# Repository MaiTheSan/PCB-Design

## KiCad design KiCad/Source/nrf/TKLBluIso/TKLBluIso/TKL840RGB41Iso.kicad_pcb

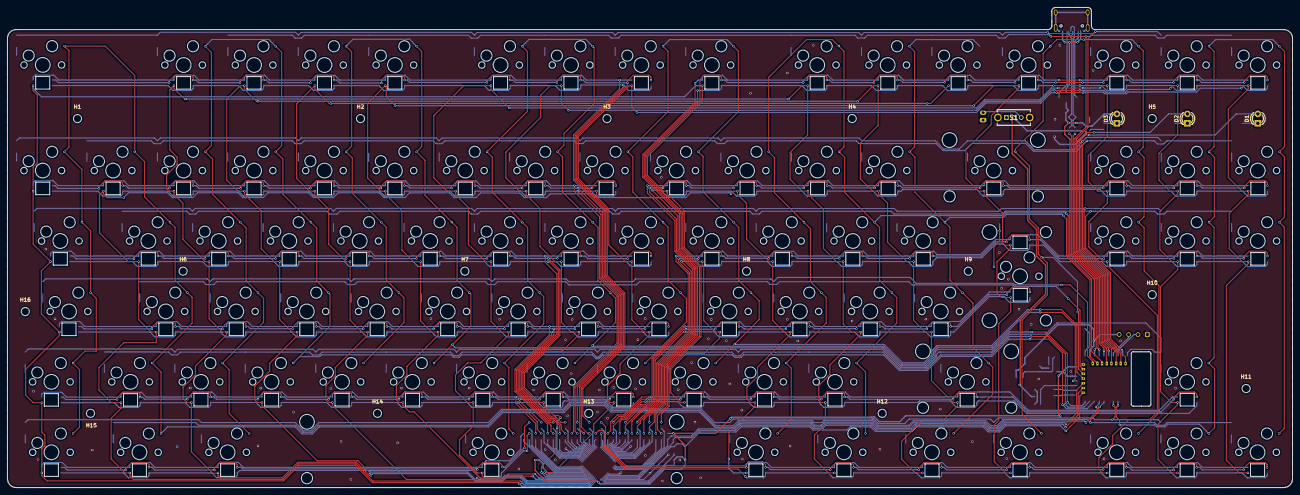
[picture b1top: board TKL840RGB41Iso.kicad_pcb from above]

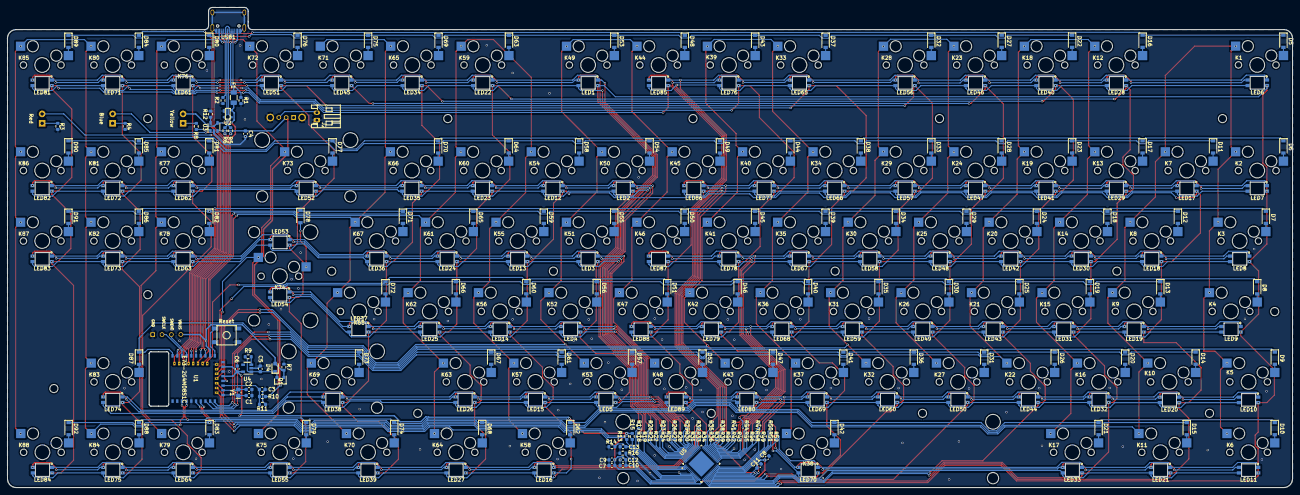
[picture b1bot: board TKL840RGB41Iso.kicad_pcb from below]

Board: 2 copper layers, 347.6 x 129.8 mm, 363 parts (255 on the bottom side), 221 nets.

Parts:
C1, C2: 22pF; C_0603_1608Metric
C3: 1nF; C_0603_1608Metric
C4, C5, C6: 10uF; C_0603_1608Metric
C7, C8, C9: 1uF; C_0603_1608Metric
C10, C11, C12, C13: 0.1uF; C_0603_1608Metric
D1: Red; LED_D3.0mm
D2: Blue; LED_D3.0mm
D3: Yellow; LED_D3.0mm
D4: 1N5819; D_SOD-323F
D5, D6, D7, D8, D9, D10, D11, D12, D13, D14, D15, D16, D17, D18, D19, D20, D21, D22, D23, D24, D25, D26, D27, D28, D29, D30, D31, D32, D33, D34, D35, D36, D37, D38, D39, D40, D41, D42, D43, D44, D45, D46, D47, D48, D49, D50, D51, D52, D53, D54, D55, D56, D57, D58, D59, D60, D61, D62, D63, D64, D65, D66, D67, D68, D69, D70, D71, D72, D73, D74, D75, D76, D77, D78, D79, D80, D81, D82, D83, D84, D85, D86, D87, D88, D89, D90, D91, D92: D; D_SOD-123
F1: 500mA; Fuse_1206_3216Metric
H1, H2, H3, H4, H5, H6, H7, H8, H9, H10, H11, H12, H13, H14, H15, H16: MountingHole; MountingHole_2.2mm_M2
J1: Conn_01x04; connector_usb
J2: Conn_01x02; JST_PH_S2B-PH-K_1x02_P2.00mm_Horizontal
K1, K2, K7, K8, K9, K10, K12, K13, K14, K15, K16, K18, K19, K20, K21, K22, K23, K24, K25, K26, K27, K28, K29, K30, K31, K32, K33, K34, K35, K36, K37, K39, K40, K41, K42, K43, K44, K45, K46, K47, K48, K49, K50, K51, K52, K53, K54, K55, K56, K57, K59, K60, K61, K62, K63, K65, K66, K67, K68, K71, K72, K76, K77, K78, K79, K80, K81, K82, K83, K84, K85, K86, K87, K88: KEYSW; MXOnly-1U-Hotswap
K3: KEYSW; MXOnly-1.5U-Hotswap
K4: KEYSW; MXOnly-1.75U-Hotswap
K5, K6, K11, K17, K58, K64, K70, K75: KEYSW; MXOnly-1.25U-Hotswap
K38: KEYSW; MXOnly-6.25U-Hotswap-ReversedStabilizers
K69: KEYSW; MXOnly-2.75U-Hotswap-ReversedStabilizers
K73, K74: KEYSW; MXOnly-2U-Hotswap-ReversedStabilizers
LED1, LED2, LED3, LED4, LED5, LED6, LED7, LED8, LED9, LED10, LED11, LED12, LED13, LED14, LED15, LED16, LED17, LED18, LED19, LED20, LED21, LED22, LED23, LED24, LED25, LED26, LED27, LED28, LED29, LED30, LED31, LED32, LED33, LED34, LED35, LED36, LED37, LED38, LED39, LED40, LED41, LED42, LED43, LED44, LED45, LED46, LED47, LED48, LED49, LED50, LED51, LED52, LED53, LED54, LED55, LED56, LED57, LED58, LED59, LED60, LED61, LED62, LED63, LED64, LED65, LED66, LED67, LED68, LED69, LED70, LED71, LED72, LED73, LED74, LED75, LED76, LED77, LED78, LED79, LED80, LED81, LED82, LED83, LED84, LED85, LED86, LED87, LED88, LED89: RGB-6028
Q1: AO3407; SOT-23
R1, R2: 5.1k; R_0603_1608Metric
R3, R4, R8, R13, R15: 1k; R_0603_1608Metric
R5, R6: 22; R_0603_1608Metric
R7, R9, R14, R16: 100k; R_0603_1608Metric
R10: 806k; R_0603_1608Metric
R11: 2M; R_0603_1608Metric
R12: 1.25k; R_0603_1608Metric
R17, R20, R23, R26, R29, R32, R35, R38, R41, R44, R47, R50: 51k; R_0603_1608Metric
R18, R19, R21, R22, R24, R25, R27, R28, R30, R31, R33, R34, R36, R37, R39, R40, R42, R43, R45, R46, R48, R49, R51, R52: 20k; R_0603_1608Metric
ResetPush1: Reset; SKQG-1155865
S1: EG1249
U1: E73-2G4M08S1C; E73-2G4M08S1C-52840
U2: PRTR5V0U2X; SOT143B
U3: MCP73831-3-OT; SOT-23-5
U4: AP2112K-3.3; SOT-23-5
U5: IS31FL3741; QFN40P700X700X80-61N
USB1: HRO-TYPE-C-31-M-12
Y1: 32.768kHz; Crystal_SMD_MicroCrystal_CM9V-T1A-2Pin_1.6x1.0mm_HandSolder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

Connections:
3.3v: C6.1, C7.1, C8.1, C9.1, C10.1, C11.1, C12.1, R13.1, R15.1, U1.19, U1.23, U4.5, U5.14, U5.15, U5.25
BLUE_LED: D2.2, U1.35
CS1: R52.1, U5.26
CS2: R51.1, U5.27
CS3: R50.1, U5.28
CS4: R49.1, U5.29
CS5: R48.1, U5.30
CS6: R47.1, U5.31
CS7: R46.1, U5.32
CS8: R45.1, U5.33
CS9: R44.1, U5.34
CS10: R43.1, U5.35
CS11: R42.1, U5.37
CS12: R41.1, U5.38
CS13: R40.1, U5.39
CS14: R39.1, U5.40
CS15: R38.1, U5.41
CS16: R37.1, U5.42
CS17: R36.1, U5.43
CS18: R35.1, U5.44
CS19: R34.1, U5.45
CS20: R33.1, U5.46
CS21: R32.1, U5.47
CS22: R31.1, U5.48
CS23: R30.1, U5.49
CS24: R29.1, U5.50
CS25: R28.1, U5.51
CS26: R27.1, U5.52
CS27: R26.1, U5.53
CS28: R25.1, U5.54
CS29: R24.1, U5.56
CS30: R23.1, U5.57
CS31: R22.1, U5.58
CS32: R21.1, U5.59
CS33: R20.1, U5.60
CS34: R19.1, U5.1
CS35: R18.1, U5.2
CS36: R17.1, U5.3
Col1: K1.1, K2.1, K3.1, K4.1, K5.1, K6.1, K7.1, K8.1, K9.1, K10.1, K11.1, U1.7
Col2: K12.1, K13.1, K14.1, K15.1, K16.1, K17.1, K18.1, K19.1, K20.1, K21.1, K22.1, U1.8
Col3: K23.1, K24.1, K25.1, K26.1, K27.1, K28.1, K29.1, K30.1, K31.1, K32.1, U1.10
Col4: K33.1, K34.1, K35.1, K36.1, K37.1, K38.1, K39.1, K40.1, K41.1, K42.1, K43.1, U1.17
Col5: K44.1, K45.1, K46.1, K47.1, K48.1, K49.1, K50.1, K51.1, K52.1, K53.1, U1.18
Col6: K54.1, K55.1, K56.1, K57.1, K58.1, K59.1, K60.1, K61.1, K62.1, K63.1, K64.1, U1.32
Col7: K65.1, K66.1, K67.1, K68.1, K69.1, K70.1, K71.1, U1.30
Col8: K72.1, K73.1, K74.1, K75.1, K76.1, K77.1, K78.1, K79.1, U1.20
Col9: K80.1, K81.1, K82.1, K83.1, K84.1, K85.1, K86.1, K87.1, K88.1, U1.3
D+: R6.2, U1.31
D-: R5.2, U1.29
DN+: R6.1, U2.2, USB1.6, USB1.8
DN-: R5.1, U2.3, USB1.5, USB1.7
GND: C1.2, C2.2, C3.2, C4.2, C5.2, C6.2, C7.2, C8.2, C9.2, C10.2, C11.2, C12.2, C13.2, J1.1, J2.1, R1.2, R2.2, R3.1, R4.1, R7.1, R11.2, R12.2, R14.2, R16.2, ResetPush1.2, S1.4, S1.5, U1.5, U1.21, U1.24, U2.1, U3.2, U4.2, U5.8, U5.12, U5.36, U5.55, USB1.1, USB1.12, USB1.13
unnamed: C1.1, U1.11, Y1.1
unnamed: C2.1, U1.13, Y1.2
unnamed: C5.1, D4.1, Q1.2, R9.1, U4.1
unnamed: D1.1, R3.2
unnamed: D2.1, R4.2
unnamed: D3.1, R8.1
unnamed: D5.2, K1.2
unnamed: D6.2, K2.2
unnamed: D7.2, K3.2
unnamed: D8.2, K4.2
unnamed: D9.2, K5.2
unnamed: D10.2, K6.2
unnamed: D11.2, K7.2
unnamed: D12.2, K8.2
unnamed: D13.2, K9.2
unnamed: D14.2, K10.2
unnamed: D15.2, K11.2
unnamed: D16.2, K12.2
unnamed: D17.2, K13.2
unnamed: D18.2, K14.2
unnamed: D19.2, K15.2
unnamed: D20.2, K16.2
unnamed: D21.2, K17.2
unnamed: D22.2, K18.2
unnamed: D23.2, K19.2
unnamed: D24.2, K20.2
unnamed: D25.2, K21.2
unnamed: D26.2, K22.2
unnamed: D27.2, K23.2
unnamed: D28.2, K24.2
unnamed: D29.2, K25.2
unnamed: D30.2, K26.2
unnamed: D31.2, K27.2
unnamed: D32.2, K28.2
unnamed: D33.2, K29.2
unnamed: D34.2, K30.2
unnamed: D35.2, K31.2
unnamed: D36.2, K32.2
unnamed: D37.2, K33.2
unnamed: D38.2, K34.2
unnamed: D39.2, K35.2
unnamed: D40.2, K36.2
unnamed: D41.2, K37.2
unnamed: D42.2, K38.2
unnamed: D43.2, K39.2
unnamed: D44.2, K40.2
unnamed: D45.2, K41.2
unnamed: D46.2, K42.2
unnamed: D47.2, K43.2
unnamed: D48.2, K44.2
unnamed: D49.2, K45.2
unnamed: D50.2, K46.2
unnamed: D51.2, K47.2
unnamed: D52.2, K48.2
unnamed: D53.2, K49.2
unnamed: D54.2, K50.2
unnamed: D55.2, K51.2
unnamed: D56.2, K52.2
unnamed: D57.2, K53.2
unnamed: D58.2, K54.2
unnamed: D59.2, K55.2
unnamed: D60.2, K56.2
unnamed: D61.2, K57.2
unnamed: D62.2, K58.2
unnamed: D63.2, K59.2
unnamed: D64.2, K60.2
unnamed: D65.2, K61.2
unnamed: D66.2, K62.2
unnamed: D67.2, K63.2
unnamed: D68.2, K64.2
unnamed: D69.2, K65.2
unnamed: D70.2, K66.2
unnamed: D71.2, K67.2
unnamed: D72.2, K68.2
unnamed: D73.2, K69.2
unnamed: D74.2, K70.2
unnamed: D75.2, K71.2
unnamed: D76.2, K72.2
unnamed: D77.2, K73.2
unnamed: D78.2, K74.2
unnamed: D79.2, K75.2
unnamed: D80.2, K76.2
unnamed: D81.2, K77.2
unnamed: D82.2, K78.2
unnamed: D83.2, K79.2
unnamed: D84.2, K80.2
unnamed: D85.2, K81.2
unnamed: D86.2, K82.2
unnamed: D87.2, K83.2
unnamed: D88.2, K84.2
unnamed: D89.2, K85.2
unnamed: D90.2, K86.2
unnamed: D91.2, K87.2
unnamed: D92.2, K88.2
unnamed: J2.2, S1.3
unnamed: LED1.2, LED22.2, LED34.2, LED45.2, LED51.2, LED61.2, LED71.2, LED81.2, R17.2
unnamed: LED1.3, LED22.3, LED34.3, LED45.3, LED51.3, LED61.3, LED71.3, LED81.3, R18.2
unnamed: LED1.4, LED22.4, LED34.4, LED45.4, LED51.4, LED61.4, LED71.4, LED81.4, R19.2
unnamed: LED10.2, LED20.2, LED32.2, LED44.2, LED50.2, LED60.2, LED69.2, LED80.2, LED89.2, R47.2
unnamed: LED10.3, LED20.3, LED32.3, LED44.3, LED50.3, LED60.3, LED69.3, LED80.3, LED89.3, R48.2
unnamed: LED10.4, LED20.4, LED32.4, LED44.4, LED50.4, LED60.4, LED69.4, LED80.4, LED89.4, R49.2
unnamed: LED11.2, LED21.2, LED33.2, LED70.2, R50.2
unnamed: LED11.3, LED21.3, LED33.3, LED70.3, R51.2
unnamed: LED11.4, LED21.4, LED33.4, LED70.4, R52.2
unnamed: LED2.2, LED12.2, LED23.2, LED35.2, LED52.2, LED62.2, LED72.2, LED82.2, R20.2
unnamed: LED2.3, LED12.3, LED23.3, LED35.3, LED52.3, LED62.3, LED72.3, LED82.3, R21.2
unnamed: LED2.4, LED12.4, LED23.4, LED35.4, LED52.4, LED62.4, LED72.4, LED82.4, R22.2
unnamed: LED3.2, LED13.2, LED24.2, LED36.2, LED53.2, LED63.2, LED73.2, LED83.2, R23.2
unnamed: LED3.3, LED13.3, LED24.3, LED36.3, LED53.3, LED63.3, LED73.3, LED83.3, R24.2
unnamed: LED3.4, LED13.4, LED24.4, LED36.4, LED53.4, LED63.4, LED73.4, LED83.4, R25.2
unnamed: LED4.2, LED14.2, LED25.2, LED37.2, LED54.2, R26.2
unnamed: LED4.3, LED14.3, LED25.3, LED37.3, LED54.3, R27.2
unnamed: LED4.4, LED14.4, LED25.4, LED37.4, LED54.4, R28.2
unnamed: LED5.2, LED15.2, LED26.2, LED38.2, LED74.2, R29.2
unnamed: LED5.3, LED15.3, LED26.3, LED38.3, LED74.3, R30.2
unnamed: LED5.4, LED15.4, LED26.4, LED38.4, LED74.4, R31.2
unnamed: LED16.2, LED27.2, LED39.2, LED55.2, LED64.2, LED75.2, LED84.2, R32.2
unnamed: LED16.3, LED27.3, LED39.3, LED55.3, LED64.3, LED75.3, LED84.3, R33.2
unnamed: LED16.4, LED27.4, LED39.4, LED55.4, LED64.4, LED75.4, LED84.4, R34.2
unnamed: LED7.2, LED17.2, LED29.2, LED41.2, LED47.2, LED57.2, LED66.2, LED77.2, LED86.2, R38.2
unnamed: LED7.3, LED17.3, LED29.3, LED41.3, LED47.3, LED57.3, LED66.3, LED77.3, LED86.3, R39.2
unnamed: LED7.4, LED17.4, LED29.4, LED41.4, LED47.4, LED57.4, LED66.4, LED77.4, LED86.4, R40.2
unnamed: LED8.2, LED18.2, LED30.2, LED42.2, LED48.2, LED58.2, LED67.2, LED78.2, LED87.2, R41.2
unnamed: LED8.3, LED18.3, LED30.3, LED42.3, LED48.3, LED58.3, LED67.3, LED78.3, LED87.3, R42.2
unnamed: LED8.4, LED18.4, LED30.4, LED42.4, LED48.4, LED58.4, LED67.4, LED78.4, LED87.4, R43.2
unnamed: LED9.2, LED19.2, LED31.2, LED43.2, LED49.2, LED59.2, LED68.2, LED79.2, LED88.2, R44.2
unnamed: LED9.3, LED19.3, LED31.3, LED43.3, LED49.3, LED59.3, LED68.3, LED79.3, LED88.3, R45.2
unnamed: LED9.4, LED19.4, LED31.4, LED43.4, LED49.4, LED59.4, LED68.4, LED79.4, LED88.4, R46.2
unnamed: LED6.2, LED28.2, LED40.2, LED46.2, LED56.2, LED65.2, LED76.2, LED85.2, R35.2
unnamed: LED6.3, LED28.3, LED40.3, LED46.3, LED56.3, LED65.3, LED76.3, LED85.3, R36.2
unnamed: LED6.4, LED28.4, LED40.4, LED46.4, LED56.4, LED65.4, LED76.4, LED85.4, R37.2
unnamed: R1.1, USB1.4
unnamed: R2.1, USB1.10
unnamed: R8.2, U3.1
unnamed: R9.2, U4.3
unnamed: R12.1, U3.5
unnamed: R16.1, U5.13
RED_LED: D1.2, U1.36
Reset: ResetPush1.1, U1.26
Row1: D5.1, D16.1, D27.1, D37.1, D48.1, D69.1, D76.1, D84.1, U1.34
Row2: D22.1, D32.1, D43.1, D53.1, D63.1, D75.1, D80.1, D89.1, U1.33
Row3: D6.1, D17.1, D28.1, D38.1, D49.1, D58.1, D70.1, D77.1, D85.1, U1.38
Row4: D11.1, D23.1, D33.1, D44.1, D54.1, D64.1, D81.1, D90.1, U1.40
Row5: D7.1, D18.1, D29.1, D39.1, D50.1, D59.1, D71.1, D78.1, D86.1, U1.42
Row6: D12.1, D24.1, D34.1, D45.1, D55.1, D65.1, D82.1, D91.1, U1.41
Row7: D8.1, D19.1, D30.1, D40.1, D51.1, D60.1, D72.1, U1.28
Row8: D13.1, D25.1, D35.1, D46.1, D56.1, D66.1, U1.22
Row9: D9.1, D20.1, D31.1, D41.1, D52.1, D61.1, D73.1, D87.1, U1.43
Row10: D14.1, D26.1, D36.1, D47.1, D57.1, D67.1, U1.9
Row11: D10.1, D21.1, D42.1, D62.1, D74.1, D79.1, D88.1, U1.4
Row12: D15.1, D68.1, D83.1, D92.1, U1.6
SCL: R13.2, U1.14, U5.10
SDA: R15.2, U1.16, U5.9
SDB: C13.1, R14.1, U1.12, U5.11
SW1: LED1.1, LED2.1, LED3.1, LED4.1, LED5.1, LED6.1, LED7.1, LED8.1, LED9.1, LED10.1, LED11.1, U5.16
SW2: LED12.1, LED13.1, LED14.1, LED15.1, LED16.1, LED17.1, LED18.1, LED19.1, LED20.1, LED21.1, U5.17
SW3: LED22.1, LED23.1, LED24.1, LED25.1, LED26.1, LED27.1, LED28.1, LED29.1, LED30.1, LED31.1, LED32.1, LED33.1, U5.18
SW4: LED34.1, LED35.1, LED36.1, LED37.1, LED38.1, LED39.1, LED40.1, LED41.1, LED42.1, LED43.1, LED44.1, U5.19
SW5: LED45.1, LED46.1, LED47.1, LED48.1, LED49.1, LED50.1, U5.20
SW6: LED51.1, LED52.1, LED53.1, LED54.1, LED55.1, LED56.1, LED57.1, LED58.1, LED59.1, LED60.1, U5.21
SW7: LED61.1, LED62.1, LED63.1, LED64.1, LED65.1, LED66.1, LED67.1, LED68.1, LED69.1, LED70.1, U5.22
SW8: LED71.1, LED72.1, LED73.1, LED74.1, LED75.1, LED76.1, LED77.1, LED78.1, LED79.1, LED80.1, U5.23
SW9: LED81.1, LED82.1, LED83.1, LED84.1, LED85.1, LED86.1, LED87.1, LED88.1, LED89.1, U5.24
SWDCLK: J1.2, U1.39
SWDIO: J1.3, U1.37
VBatt: C4.1, Q1.3, R10.1, S1.2, U3.3
VBatt_Monitor: C3.1, R10.2, R11.1, U1.15
VBus: D3.2, D4.2, F1.1, J1.4, Q1.1, R7.2, U1.27, U2.4, U3.4
VCC: F1.2, USB1.2, USB1.11

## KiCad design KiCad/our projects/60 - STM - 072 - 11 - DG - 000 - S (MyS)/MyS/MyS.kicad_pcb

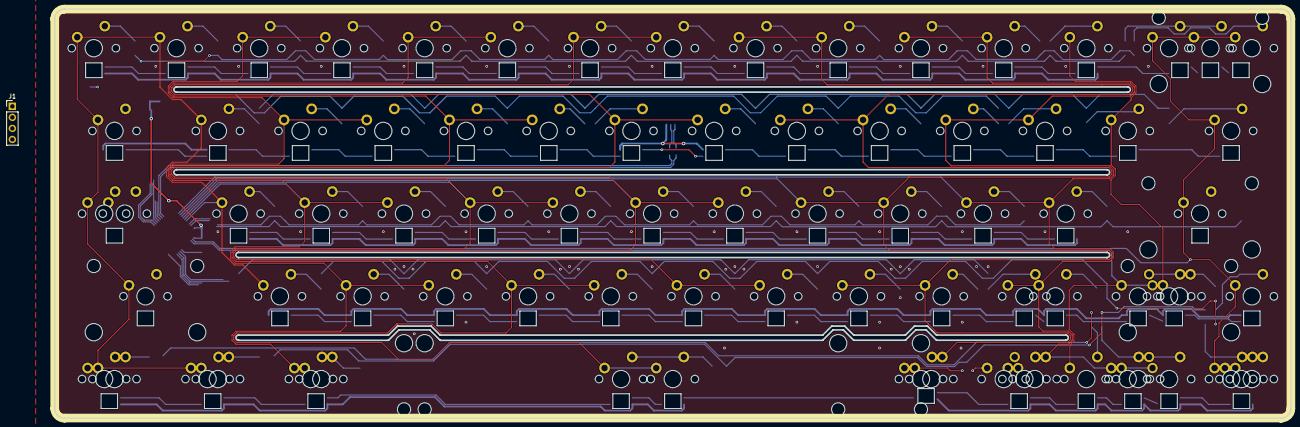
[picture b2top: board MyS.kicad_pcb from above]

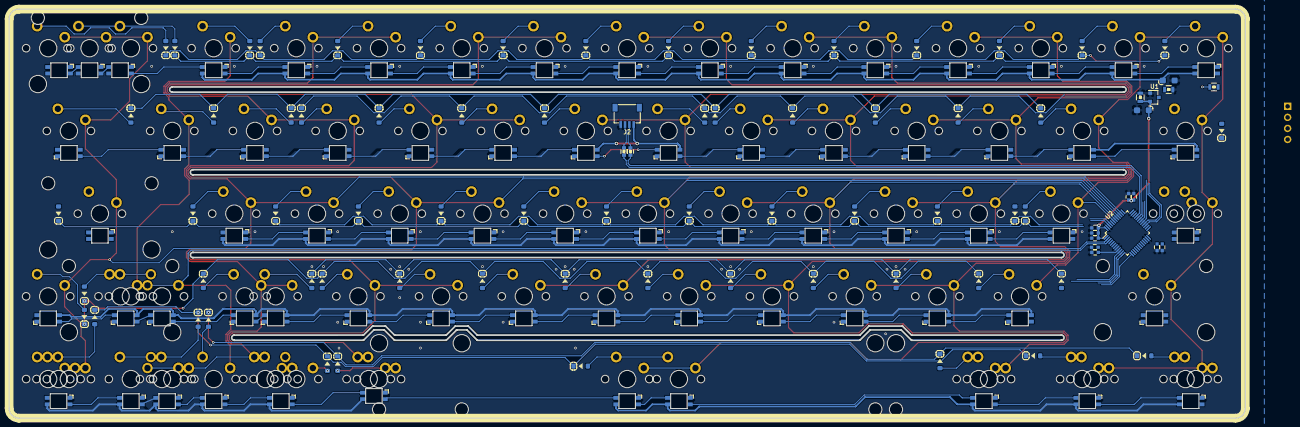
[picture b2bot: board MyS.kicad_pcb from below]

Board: 2 copper layers, 284.7 x 94.2 mm, 234 parts (153 on the bottom side), 160 nets.

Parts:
C1, C2: 1uF; CP_EIA-3216
C21, C23, C25, C27: 0.1uF; C_0603
C22, C24, C26: 1uF; C_0603
C28: 4.7uF; C_0603
C29: 10nF; C_0603
D1, D2, D3, D4, D5, D6, D7, D8, D9, D10, D11, D12, D13, D14, D15, D16, D17, D18, D19, D20, D21, D22, D23, D24, D25, D26, D27, D28, D29, D30, D31, D32, D33, D34, D35, D36, D37, D38, D39, D40, D41, D42, D43, D45, D46, D48, D49, D50, D51, D52, D53, D54, D55, D56, D57, D58, D59, D61, D62, D63, D65, D70, D71, D72, D73: D; D_SOD-123
J1: Conn_01x04_Female; PinHeader_1x04_P2.54mm_Vertical
J2: Conn_01x04_Female; JST-SR-4
MX1, MX2, MX3, MX4, MX5, MX6, MX7, MX8, MX9, MX10, MX11, MX12, MX13, MX14, MX15, MX16, MX19, MX20, MX21, MX22, MX23, MX24, MX25, MX26, MX27, MX28, MX29, MX30, MX34, MX35, MX36, MX37, MX38, MX39, MX40, MX41, MX42, MX43, MX44, MX45, MX49, MX50, MX51, MX52, MX53, MX54, MX55, MX56, MX57, MX58, MX59, MX61, MX69, MX76, MX77, MX78, MX80: 1U; MXOnly-1U-NoLED
MX17: 2U; MXOnly-2U-NoLED
MX18, MX33, MX46, MX70, MX72, MX79: 1.5U; MXOnly-1.5U-NoLED
MX31: 1.25U-stepcap; MXOnly-1.25U-NoLED
MX32, MX60, MX82: 1.75U; MXOnly-1.75U-NoLED
MX47, MX48: 2.25U; MXOnly-2.25U-NoLED
MX62, MX65, MX66, MX67, MX73, MX74, MX75: 1.25U; MXOnly-1.25U-NoLED
MX68: 6.25U; MXOnly-6.25U-ReversedStabilizers-NoLED
MX71: 6.25U; MXOnly-7U-ReversedStabilizers-NoLED
MX81: 2.25U; MXOnly-2.75U-NoLED
R1, R2: 100k; R_0805
R3, R4: 22; R_0603
R7: 330R; R_0805
RGB1, RGB2, RGB3, RGB4, RGB5, RGB6, RGB7, RGB8, RGB9, RGB10, RGB11, RGB12, RGB13, RGB14, RGB15, RGB16, RGB17, RGB18, RGB33, RGB34, RGB35, RGB36, RGB37, RGB38, RGB39, RGB40, RGB41, RGB42, RGB43, RGB45, RGB46, RGB61, RGB62, RGB63, RGB64, RGB65, RGB66, RGB67, RGB68, RGB69: SK6812; RGB-6028_FLIPPED
RGB19, RGB20, RGB21, RGB22, RGB23, RGB24, RGB25, RGB26, RGB27, RGB28, RGB29, RGB30, RGB31, RGB32: SK6812_FL; RGB-6028
SK6812_FL1, SK6812_FL2, SK6812_FL3, SK6812_FL4, SK6812_FL5, SK6812_FL6, SK6812_FL7, SK6812_FL8, SK6812_FL9, SK6812_FL10, SK6812_FL11, SK6812_FL12, SK6812_FL13, SK6812_FL14, SK6812_FL15: SK6812; RGB-6028
U1: MCP1700-3302E / MCP1703A-3302 (SOT23); SOT-23
U2: STM32F072C8Tx; LQFP-48_7x7mm_P0.5mm

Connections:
+3V3: C2.1, C21.1, C22.2, C23.2, C24.2, C25.2, C26.2, C27.2, C28.1, C29.1, R2.1, U1.2, U2.1, U2.9, U2.24, U2.36, U2.48
+5V: C1.1, J1.1, J2.1, R1.1, RGB1.1, RGB2.1, RGB3.1, RGB4.1, RGB5.1, RGB6.1, RGB7.1, RGB8.1, RGB9.1, RGB10.1, RGB11.1, RGB12.1, RGB13.1, RGB14.1, RGB15.1, RGB16.1, RGB17.1, RGB18.1, RGB19.1, RGB20.1, RGB21.1, RGB22.1, RGB23.1, RGB24.1, RGB25.1, RGB26.1, RGB27.1, RGB28.1, RGB29.1, RGB30.1, RGB31.1, RGB32.1, RGB33.1, RGB34.1, RGB35.1, RGB36.1, RGB37.1, RGB38.1, RGB39.1, RGB40.1, RGB41.1, RGB42.1, RGB43.1, RGB45.1, RGB46.1, RGB61.1, RGB62.1, RGB63.1, RGB64.1, RGB65.1, RGB66.1, RGB67.1, RGB68.1, RGB69.1, SK6812_FL1.1, SK6812_FL2.1, SK6812_FL3.1, SK6812_FL4.1, SK6812_FL5.1, SK6812_FL6.1, SK6812_FL7.1, SK6812_FL8.1, SK6812_FL9.1, SK6812_FL10.1, SK6812_FL11.1, SK6812_FL12.1, SK6812_FL13.1, SK6812_FL14.1, SK6812_FL15.1, U1.3
Col0: MX1.1, MX2.1, MX18.1, MX19.1, MX31.1, MX32.1, MX35.1, MX46.1, MX47.1, MX49.1, MX65.1, MX66.1, MX69.1, U2.43
Col1: MX3.1, MX4.1, MX20.1, MX21.1, MX36.1, MX37.1, MX51.1, MX52.1, MX67.1, MX70.1, U2.42
Col2: MX5.1, MX6.1, MX22.1, MX23.1, MX38.1, MX39.1, MX53.1, MX54.1, MX68.1, MX71.1, U2.41
Col3: MX7.1, MX8.1, MX24.1, MX25.1, MX40.1, MX41.1, MX55.1, MX56.1, U2.40
Col4: MX9.1, MX10.1, MX16.2, MX26.1, MX27.1, MX42.1, MX43.1, MX57.1, MX58.1, MX74.2, U2.39
Col5: MX11.1, MX12.1, MX28.1, MX29.1, MX34.2, MX44.1, MX45.1, MX59.1, MX60.1, MX62.1, MX72.2, MX75.2, MX76.1, MX78.1, U2.38
Col6: MX13.1, MX30.1, MX50.1, MX80.1, MX81.1, MX82.1, U2.3
Col7: MX14.1, MX15.1, MX17.1, MX33.1, MX48.1, MX61.1, MX73.1, MX77.1, MX79.1, U2.2
D+: R3.1, U2.33
D-: R4.1, U2.32
DG+: J2.3, R3.2
DG-: J2.2, R4.2
GND: C1.2, C2.2, C21.2, C22.1, C23.1, C24.1, C25.1, C26.1, C27.1, C28.2, C29.2, J1.4, J2.4, R1.2, R2.2, RGB1.3, RGB2.3, RGB3.3, RGB4.3, RGB5.3, RGB6.3, RGB7.3, RGB8.3, RGB9.3, RGB10.3, RGB11.3, RGB12.3, RGB13.3, RGB14.3, RGB15.3, RGB16.3, RGB17.3, RGB18.3, RGB19.3, RGB20.3, RGB21.3, RGB22.3, RGB23.3, RGB24.3, RGB25.3, RGB26.3, RGB27.3, RGB28.3, RGB29.3, RGB30.3, RGB31.3, RGB32.3, RGB33.3, RGB34.3, RGB35.3, RGB36.3, RGB37.3, RGB38.3, RGB39.3, RGB40.3, RGB41.3, RGB42.3, RGB43.3, RGB45.3, RGB46.3, RGB61.3, RGB62.3, RGB63.3, RGB64.3, RGB65.3, RGB66.3, RGB67.3, RGB68.3, RGB69.3, SK6812_FL1.3, SK6812_FL2.3, SK6812_FL3.3, SK6812_FL4.3, SK6812_FL5.3, SK6812_FL6.3, SK6812_FL7.3, SK6812_FL8.3, SK6812_FL9.3, SK6812_FL10.3, SK6812_FL11.3, SK6812_FL12.3, SK6812_FL13.3, SK6812_FL14.3, SK6812_FL15.3, U1.1, U2.8, U2.23, U2.35, U2.47
unnamed: D1.2, MX1.2
unnamed: D2.2, MX2.2
unnamed: D3.2, MX3.2
unnamed: D4.2, MX4.2
unnamed: D5.2, MX5.2
unnamed: D6.2, MX6.2
unnamed: D7.2, MX7.2
unnamed: D8.2, MX8.2
unnamed: D9.2, MX9.2
unnamed: D10.2, MX10.2
unnamed: D11.2, MX11.2
unnamed: D12.2, MX12.2
unnamed: D13.2, MX13.2
unnamed: D14.2, MX14.2, MX17.2
unnamed: D15.2, MX15.2
unnamed: D16.2, MX50.2
unnamed: D17.2, MX18.2
unnamed: D18.2, MX19.2
unnamed: D19.2, MX20.2
unnamed: D20.2, MX21.2
unnamed: D21.2, MX22.2
unnamed: D22.2, MX23.2
unnamed: D23.2, MX24.2
unnamed: D24.2, MX25.2
unnamed: D25.2, MX26.2
unnamed: D26.2, MX27.2
unnamed: D27.2, MX28.2
unnamed: D28.2, MX29.2
unnamed: D29.2, MX30.2
unnamed: D30.2, MX31.2, MX32.2
unnamed: D31.2, MX33.2
unnamed: D32.2, MX80.2, MX81.2, MX82.2
unnamed: D33.2, MX35.2
unnamed: D34.2, MX36.2
unnamed: D35.2, MX37.2
unnamed: D36.2, MX38.2
unnamed: D37.2, MX39.2
unnamed: D38.2, MX40.2
unnamed: D39.2, MX41.2
unnamed: D40.2, MX42.2
unnamed: D41.2, MX43.2
unnamed: D42.2, MX44.2
unnamed: D43.2, MX45.2
unnamed: D45.2, MX48.2
unnamed: D46.2, MX47.2
unnamed: D48.2, MX49.2
unnamed: D49.2, MX51.2
unnamed: D50.2, MX52.2
unnamed: D51.2, MX53.2
unnamed: D52.2, MX54.2
unnamed: D53.2, MX55.2
unnamed: D54.2, MX56.2
unnamed: D55.2, MX57.2
unnamed: D56.2, MX58.2
unnamed: D57.2, MX59.2
unnamed: D58.2, MX60.2
unnamed: D59.2, MX61.2
unnamed: D61.2, MX46.2, MX65.2
unnamed: D62.2, MX66.2, MX69.2
unnamed: D63.2, MX67.2, MX70.2
unnamed: D65.2, MX68.2, MX71.2
unnamed: D70.2, MX16.1, MX74.1
unnamed: D71.2, MX34.1, MX72.1, MX75.1
unnamed: D72.2, MX62.2, MX76.2, MX78.2
unnamed: D73.2, MX73.2, MX77.2, MX79.2
unnamed: RGB1.2, RGB2.4
unnamed: RGB2.2, RGB3.4
unnamed: RGB3.2, RGB4.4
unnamed: RGB4.2, RGB5.4
unnamed: RGB5.2, RGB6.4
unnamed: RGB6.2, RGB7.4
unnamed: RGB7.2, RGB8.4
unnamed: RGB8.2, RGB9.4
unnamed: RGB10.2, RGB11.4
unnamed: RGB9.2, RGB10.4
unnamed: RGB11.2, RGB12.4
unnamed: RGB12.2, RGB13.4
unnamed: RGB13.2, RGB14.4
unnamed: RGB14.2, RGB15.4
unnamed: RGB15.2, RGB16.4
unnamed: RGB16.2, RGB32.4
unnamed: RGB17.2, RGB18.4
unnamed: RGB17.4, RGB19.2
unnamed: RGB18.2, RGB33.4
unnamed: RGB19.4, RGB20.2
unnamed: RGB20.4, RGB21.2
unnamed: RGB21.4, RGB22.2
unnamed: RGB22.4, RGB23.2
unnamed: RGB23.4, RGB24.2
unnamed: RGB24.4, RGB25.2
unnamed: RGB25.4, RGB26.2
unnamed: RGB26.4, RGB27.2
unnamed: RGB27.4, RGB28.2
unnamed: RGB28.4, RGB29.2
unnamed: RGB29.4, RGB30.2
unnamed: RGB30.4, RGB31.2
unnamed: RGB31.4, RGB32.2
unnamed: RGB33.2, RGB34.4
unnamed: RGB34.2, RGB35.4
unnamed: RGB35.2, RGB36.4
unnamed: RGB36.2, RGB37.4
unnamed: RGB37.2, RGB38.4
unnamed: RGB38.2, RGB39.4
unnamed: RGB39.2, RGB40.4
unnamed: RGB40.2, RGB41.4
unnamed: RGB41.2, RGB42.4
unnamed: RGB42.2, RGB43.4
unnamed: RGB43.2, SK6812_FL15.4
unnamed: RGB45.2, RGB46.4
unnamed: RGB45.4, SK6812_FL1.2
unnamed: RGB46.2, RGB61.4
unnamed: RGB61.2, RGB62.4
unnamed: RGB62.2, RGB63.4
unnamed: RGB63.2, RGB64.4
unnamed: RGB64.2, RGB65.4
unnamed: RGB65.2, RGB66.4
unnamed: RGB66.2, RGB67.4
unnamed: RGB67.2, RGB68.4
unnamed: RGB68.2, RGB69.4
unnamed: SK6812_FL1.4, SK6812_FL2.2
unnamed: SK6812_FL2.4, SK6812_FL3.2
unnamed: SK6812_FL3.4, SK6812_FL4.2
unnamed: SK6812_FL4.4, SK6812_FL5.2
unnamed: SK6812_FL5.4, SK6812_FL6.2
unnamed: SK6812_FL6.4, SK6812_FL7.2
unnamed: SK6812_FL7.4, SK6812_FL8.2
unnamed: SK6812_FL8.4, SK6812_FL9.2
unnamed: SK6812_FL9.4, SK6812_FL10.2
unnamed: SK6812_FL10.4, SK6812_FL11.2
unnamed: SK6812_FL11.4, SK6812_FL12.2
unnamed: SK6812_FL12.4, SK6812_FL13.2
unnamed: SK6812_FL13.4, SK6812_FL14.2
unnamed: SK6812_FL14.4, SK6812_FL15.2
Row0: D1.1, D3.1, D5.1, D7.1, D9.1, D11.1, D13.1, D14.1
Row1: D2.1, D4.1, D6.1, D8.1, D10.1, D12.1, D15.1
Row2: D17.1, D19.1, D21.1, D23.1, D25.1, D27.1
Row3: D18.1, D20.1, D22.1, D24.1, D26.1, D28.1, D29.1, D31.1
Row4: D30.1, D34.1, D36.1, D38.1, D40.1, D42.1
Row5: D33.1, D35.1, D37.1, D39.1, D41.1, D43.1, D45.1
Row6: D46.1, D49.1, D51.1, D53.1, D55.1, D57.1
Row7: D32.1, D48.1, D50.1, D52.1, D54.1, D56.1, D58.1, D59.1
Row8: D16.1, D61.1, D63.1, D70.1
Row9: D62.1, D65.1, D71.1, D72.1, D73.1
SWCLK: J1.2, U2.37
SWDIO: J1.3, U2.34

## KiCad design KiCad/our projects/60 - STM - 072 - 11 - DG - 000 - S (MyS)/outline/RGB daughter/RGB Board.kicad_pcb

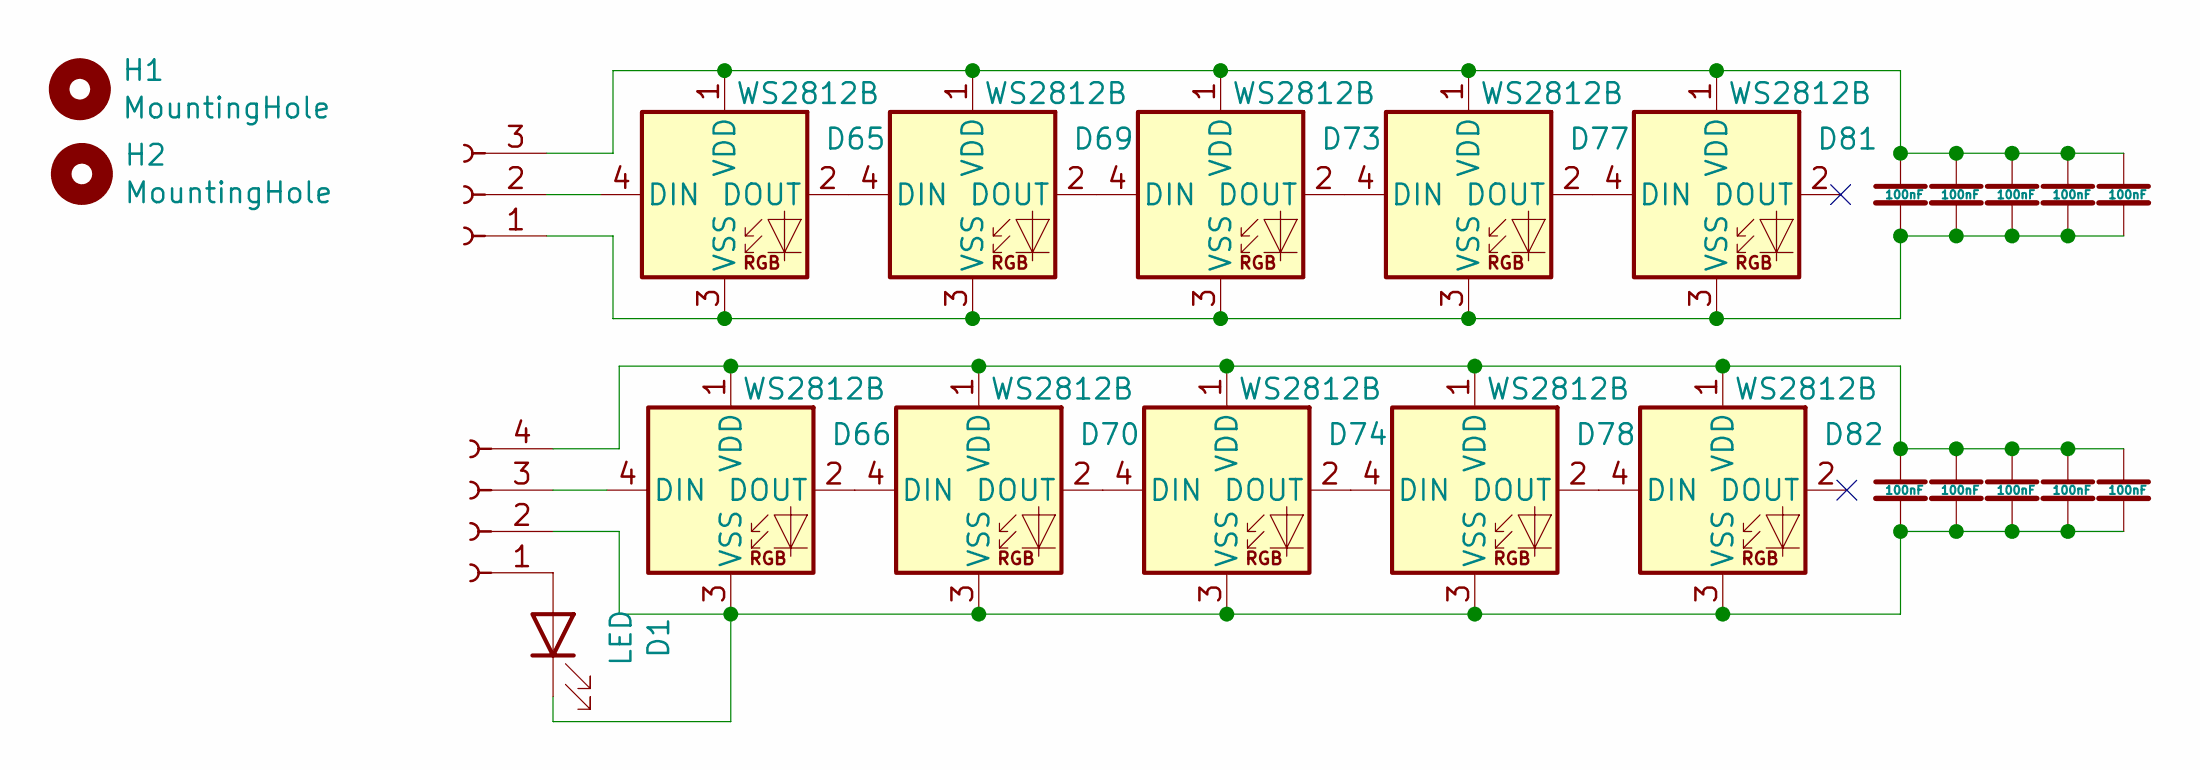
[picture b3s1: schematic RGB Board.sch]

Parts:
C_RGB13, C_RGB14, C_RGB15, C_RGB16, C_RGB17, C_RGB18, C_RGB19, C_RGB20, C_RGB21, C_RGB22: 100nF; C_0805_2012Metric
D1: LED; LED_1206_3216Metric
D65, D66, D69, D70, D73, D74, D77, D78, D81, D82: WS2812B; SK6812_miniE
H1, H2: MountingHole; HOLE_M2.6
J1: Conn_01x04_Female; JST_SH_SM04B-SRSS-TB_1x04-1MP_P1.00mm_Horizontal
RGB_UP4: Conn_01x03_Female; JST_SH_SM03B-SRSS-TB_1x03-1MP_P1.00mm_Horizontal

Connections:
unnamed: C_RGB13.1, C_RGB15.1, C_RGB17.1, C_RGB19.1, C_RGB21.1, D65.1 (VDD), D69.1 (VDD), D73.1 (VDD), D77.1 (VDD), D81.1 (VDD), RGB_UP4.3
unnamed: C_RGB13.2, C_RGB15.2, C_RGB17.2, C_RGB19.2, C_RGB21.2, D65.3 (VSS), D69.3 (VSS), D73.3 (VSS), D77.3 (VSS), D81.3 (VSS), RGB_UP4.1
unnamed: C_RGB14.1, C_RGB16.1, C_RGB18.1, C_RGB20.1, C_RGB22.1, D66.1 (VDD), D70.1 (VDD), D74.1 (VDD), D78.1 (VDD), D82.1 (VDD), J1.4
unnamed: C_RGB14.2, C_RGB16.2, C_RGB18.2, C_RGB20.2, C_RGB22.2, D1.1 (K), D66.3 (VSS), D70.3 (VSS), D74.3 (VSS), D78.3 (VSS), D82.3 (VSS), J1.2
unnamed: D1.2 (A), J1.1
unnamed: D65.2 (DOUT), D69.4 (DIN)
unnamed: D65.4 (DIN), RGB_UP4.2
unnamed: D66.2 (DOUT), D70.4 (DIN)
unnamed: D66.4 (DIN), J1.3
unnamed: D69.2 (DOUT), D73.4 (DIN)
unnamed: D70.2 (DOUT), D74.4 (DIN)
unnamed: D73.2 (DOUT), D77.4 (DIN)
unnamed: D74.2 (DOUT), D78.4 (DIN)
unnamed: D77.2 (DOUT), D81.4 (DIN)
unnamed: D78.2 (DOUT), D82.4 (DIN)

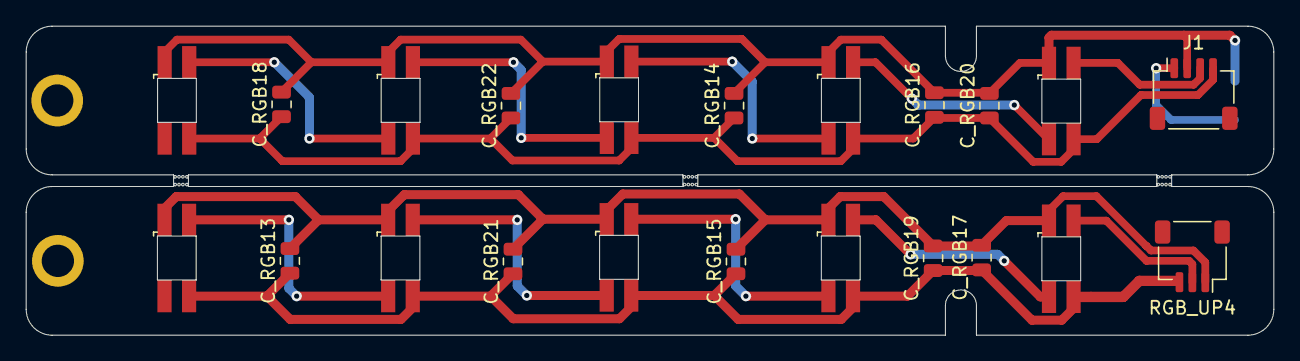
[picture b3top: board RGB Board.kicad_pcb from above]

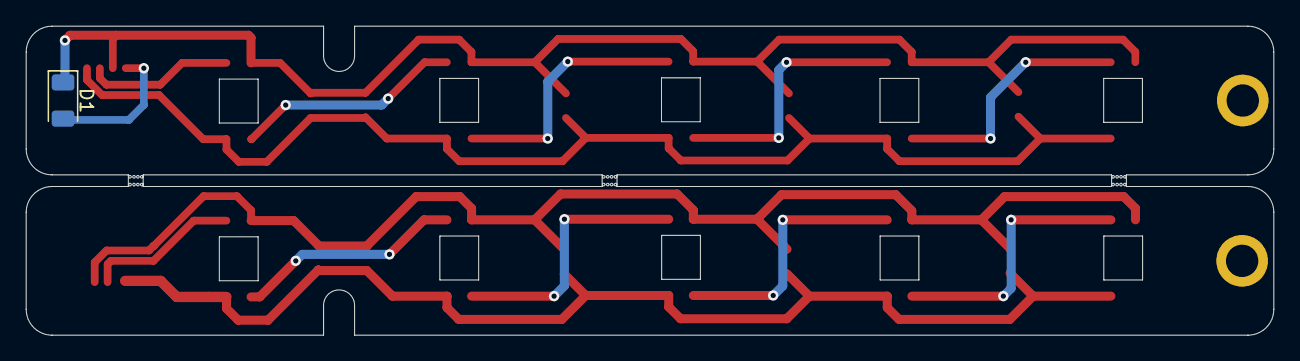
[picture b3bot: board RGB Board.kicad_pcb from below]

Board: 2 copper layers, 96.5 x 23.9 mm, 25 parts (11 on the bottom side), 15 nets.
